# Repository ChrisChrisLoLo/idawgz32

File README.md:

# idawgz32

### A mechanical keyboard, in this economy??

An experimental ultraportable and ultra affordable pocket keyboard that costs $5 worth of materials to make. The project goal is to make a keyboard that can be given away as freebies or gifts. Entire PCBA can be produced by JLCPCB. Uses a CH552 as its MCU, and runs FAK firmware.

# Status
v2.0 PCBs are working well and is recommended to try out! v0.0 PCBs use a switch that has a high defect rate. the v2.0 switches use a much more reliable switch.

I recommend using v2.0, though v0.0 has some workarounds outlined in my blog post.

Disclaimer is that this design has very low tolerances for its key switches. You will likely need a 3D printer such as a Bambu Lab A1/A1 mini/P1P/P1S and set the slicing layer resolution to 0.08mm. Printers like the Prusa i3/mini may also work, but have not been tested.

# About
I got excited with the new recent trend of building keyboards with the CH552 chip, and wanted to expand on my [pusheenz40](https://github.com/ChrisChrisLoLo/pusheenz40) design, with the end goal of building a keyboard that costs so little that I can freely give it away as a small gift or as a freebie at conventions. The size of the board, layout, and component selection (or lack there of) are all in service of getting the price as low as possible.

You can read more about the experiment and the design process in my blog post here: https://chrischrislolo.github.io/orthoLabLogs/idawgs32-how-i-made-a-full-keyboard-for-dollar6.html

Case files include 3MF files, STEP files that include the top case housing, as well as the buttons.

# Case
The case files can be found in the `case` directory.

3D printed cases can and should use the finest resolution possible on your printer, and ideally should use a higher end printer due to it's low tolerances. The models have been tested to work with the Bambu lab A1 and P1S at a layer height and detail setting of 0.08mm (extra fine). It's recommended to use a high quality and/or a newer printer.

Lubricating the case rails with something like krytox 205g0 is highly recommended (and a near must for v0.0 boards), especially when using a CNC aluminum case. 

## PCB
You can find the PCB source files in the `pcb` folder. The BOM files can be found in this folder.

## Directory Structure
- `case`
    You can find the files you need in this folder to print out a case for the keyboard
- `drafts`
    Stores any ergogen or intermediate information used in making the case
- `pcb`
    Kicad project relating to the project. Contains the BOM, placement files, and gerbers
   
## BOM
- 1 PCBA
  - The PCB will include all electrical parts required, including switches.
- 1 Aluminum CNC upper case or 3DP upper case
- 32 3D printed buttons
- 8 3mm M1.6 screws (go for flathead for a more flush fit, though other head types should also work)
- 4-8 (ideally 8) 1-2mm bumpons (something like Sj5302 is a good place to start)

## Assembly
Flash the pcb with my FAK branch (see below section). Bootmagic is enabled, so using the top left key to flash from here on out is doable.

Pop the 3D printed buttons/keycaps into the case, and make sure they don't stick and can freely move up and down. If they do stick (e.g. need noticable force applied to pop out), confirm that you're printing at the finest detail setting. All keys need to be flush against the case. Once the switches are in place, over lap the pcb over the case. Gently press the pcb to make sure a button isn't pressed down.

Optionally wrap the board with a rubber band to hold it in place and flip it over to validate everything. Then gently press every button to make sure if it can actuate. If a button is very sticky, reprinting or sanding may be required. If there's slight friction on the keys return, this should slowly go away as the keyboard is broken in. If there's a button that won't actuate, it's possible that the button is misaligned. Flip the board back around, remove the rubber band and pcb, and make sure the problematic key is flush against the case. Place back pcb around and test until all keys properly acutate.

Then turn the keybard around one last time so the pcb is facing upwards. Screw on the screws and test one last time.

Finally, place on the rubber bumpons

## Firmware
Branch and fork of FAK Firmware can be found here:
https://github.com/ChrisChrisLoLo/fak/tree/idawgz32

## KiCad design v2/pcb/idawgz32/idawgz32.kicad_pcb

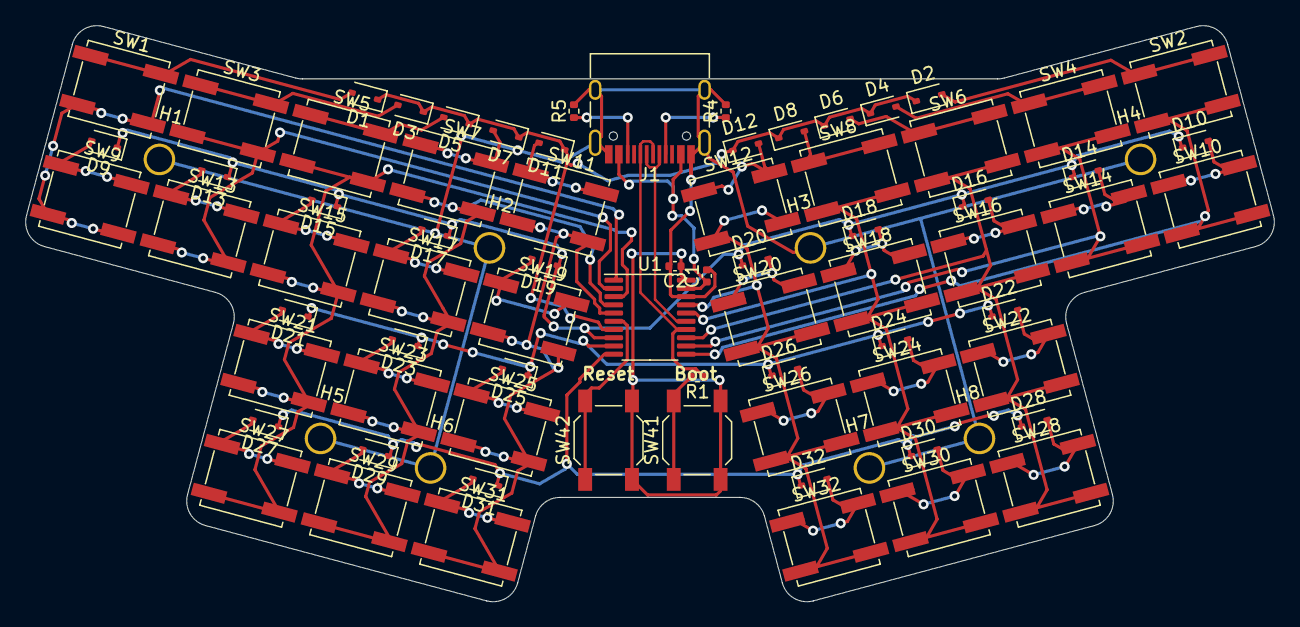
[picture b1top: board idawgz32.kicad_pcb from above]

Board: 2 copper layers, 98.7 x 45.5 mm, 81 parts (0 on the bottom side), 55 nets.

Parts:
C1, C2: 100nF; C_0402_1005Metric
D1, D2, D3, D4, D5, D6, D7, D8, D9, D10, D11, D12, D13, D14, D15, D16, D17, D18, D19, D20, D21, D22, D23, D24, D25, D26, D27, D28, D29, D30, D31, D32: D_Small; D_SOD-323
H1, H2, H3, H4, H5, H6, H7, H8: MountingHole_Pad; m1.6_hole
J1: USB_C_Receptacle_USB2.0; USB_C_Receptacle_HRO_TYPE-C-31-M-12
R1: 10k; R_0402_1005Metric
R4, R5: 5.1k; R_0402_1005Metric
SW1, SW2, SW3, SW4, SW5, SW6, SW7, SW8, SW9, SW10, SW11, SW12, SW13, SW14, SW15, SW16, SW17, SW18, SW19, SW20, SW21, SW22, SW23, SW24, SW25, SW26, SW27, SW28, SW29, SW30, SW31, SW32: SW_Push; SW_SPST_EVQP0
SW41: BOOT; SW_SPST_SKQG_WithStem
SW42: RESET; SW_SPST_SKQG_WithStem
U1: CH552T; TSSOP-20_4.4x6.5mm_P0.65mm

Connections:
+3.3V: C2.1, SW41.2, SW42.2, U1.20 (V33)
BOOT: R1.2, SW41.1
CC1: J1.A5 (CC1), R4.1
CC2: J1.B5 (CC2), R5.1
GND: C1.2, C2.2, H1.1, H2.1, H3.1, H4.1, H5.1, H6.1, H7.1, H8.1, J1.A1 (GND), J1.A12 (GND), J1.B1 (GND), J1.B12 (GND), J1.S1 (SHIELD), R4.2, R5.2, U1.18 (GND/VSS)
unnamed: D1.2 (A), SW1.1
unnamed: D2.2 (A), SW2.1
unnamed: D3.2 (A), SW3.1
unnamed: D4.2 (A), SW4.1
unnamed: D5.2 (A), SW5.1
unnamed: D6.2 (A), SW6.1
unnamed: D7.2 (A), SW7.1
unnamed: D8.2 (A), SW8.1
unnamed: D9.2 (A), SW9.1
unnamed: D10.2 (A), SW10.1
unnamed: D11.2 (A), SW11.1
unnamed: D12.2 (A), SW12.1
unnamed: D13.2 (A), SW13.1
unnamed: D14.2 (A), SW14.1
unnamed: D15.2 (A), SW15.1
unnamed: D16.2 (A), SW16.1
unnamed: D17.2 (A), SW17.1
unnamed: D18.2 (A), SW18.1
unnamed: D19.2 (A), SW19.1
unnamed: D20.2 (A), SW20.1
unnamed: D21.2 (A), SW21.1
unnamed: D22.2 (A), SW22.1
unnamed: D23.2 (A), SW23.1
unnamed: D24.2 (A), SW24.1
unnamed: D25.2 (A), SW25.1
unnamed: D26.2 (A), SW26.1
unnamed: D27.2 (A), SW27.1
unnamed: D28.2 (A), SW28.1
unnamed: D29.2 (A), SW29.1
unnamed: D30.2 (A), SW30.1
unnamed: D31.2 (A), SW31.1
unnamed: D32.2 (A), SW32.1
RST: SW42.1, U1.6 (RST/T2EX_/CAP2_)
UDM: J1.A7 (D-), J1.B7 (D-), U1.15 (P3.7/UDM)
UDP: J1.A6 (D+), J1.B6 (D+), R1.1, U1.14 (P3.6/UDP)
VBUS: C1.1, J1.A4 (VBUS), J1.A9 (VBUS), J1.B4 (VBUS), J1.B9 (VBUS), U1.19 (VCC/VDD)
col1: SW1.2, SW9.2, U1.1 (P3.2/TXD1_/INT0/VBUS1/AIN3)
col2: SW3.2, SW13.2, U1.2 (P1.4/T2_/CAP1_/SCS/TIN2/UCC1/AIN1)
col3: SW5.2, SW15.2, SW21.2, SW27.2, U1.3 (P1.5/MOSI/PWM1/TIN3/UCC2/AIN2)
col4: SW7.2, SW17.2, SW23.2, SW29.2, U1.4 (P1.6/MISO/RXD1/TIN4)
col5: SW11.2, SW19.2, SW25.2, SW31.2, U1.5 (P1.7/SCK/TXD1/TIN5)
col6: SW12.2, SW20.2, SW26.2, SW32.2, U1.17 (P1.2/XI/RXD_)
col7: SW8.2, SW18.2, SW24.2, SW30.2, U1.16 (P1.3/XO/TXD_)
col8: SW6.2, SW16.2, SW22.2, SW28.2, U1.13 (P3.5/T1)
col9: SW4.2, SW14.2, U1.12 (P3.4/PWM2/RXD1_/T0)
col10: SW2.2, SW10.2, U1.11 (P3.3/INT1)
row1: D1.1 (K), D2.1 (K), D3.1 (K), D4.1 (K), D5.1 (K), D6.1 (K), D7.1 (K), D8.1 (K), D11.1 (K), D12.1 (K), U1.7 (P1.0/T2/CAP1/TIN0)
row2: D9.1 (K), D10.1 (K), D13.1 (K), D14.1 (K), D15.1 (K), D16.1 (K), D17.1 (K), D18.1 (K), D19.1 (K), D20.1 (K), U1.8 (P1.1/T2EX/CAP2/TIN1/VBUS2/AIN0)
row3: D21.1 (K), D22.1 (K), D23.1 (K), D24.1 (K), D25.1 (K), D26.1 (K), U1.9 (P3.1/PWM2_/TXD)
row4: D27.1 (K), D28.1 (K), D29.1 (K), D30.1 (K), D31.1 (K), D32.1 (K), U1.10 (P3.0/PWM1_/RXD)

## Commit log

2024-01-21 add init ergogen
2024-01-22 init pcb
2024-01-29 update gerbers
2024-02-19 add schematic
2024-02-25 add v2 pcb
2024-02-26 add photos
2024-02-26 init README.md
2024-03-31 finalize v2
2024-03-31 update wording
2024-10-14 update case file
